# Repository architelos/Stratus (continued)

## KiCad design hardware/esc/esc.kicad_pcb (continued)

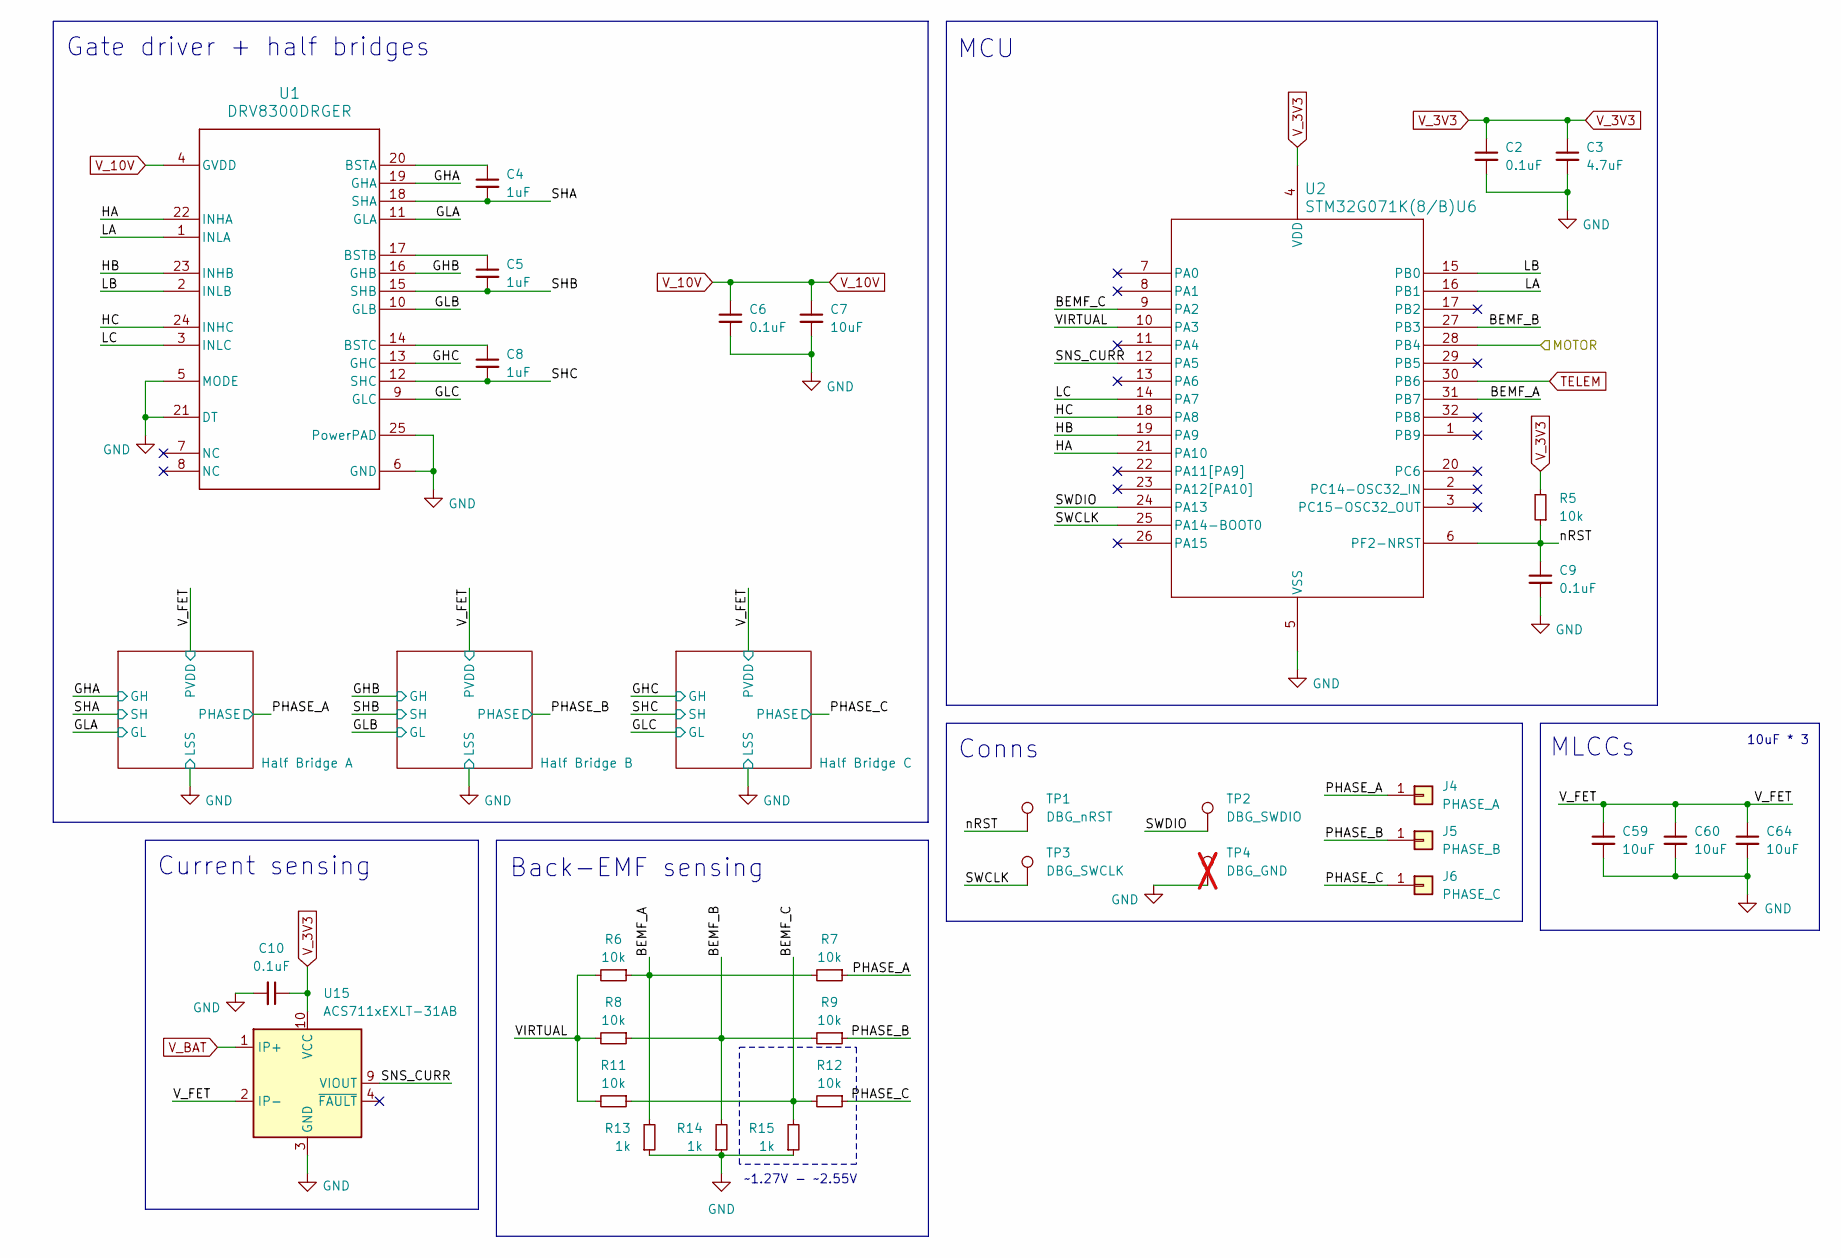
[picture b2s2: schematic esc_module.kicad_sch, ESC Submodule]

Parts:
C2, C6, C9, C10: 0.1uF; C_0402; MPN CGA2B3X7R1V104KT0Y0F; LCSC# C343047
C3: 4.7uF; C_0402; MPN TDK105CBJ475MV-F; LCSC# C22385335
C4, C5, C8: 1uF; C_0402; MPN GRM155R6YA105KE11J; LCSC# C3835721
C7: 10uF; C_1206_3216Metric; MPN GRT31CR6YA106KE01L; LCSC# C2175512
C59, C60, C64: 10uF; C_0805_2012Metric; MPN GRM21BR6YA106KE43L; LCSC# C162422
J4: PHASE_A; Phase_Pad_3x3_D1.5
J5: PHASE_B; Phase_Pad_3x3_D1.5
J6: PHASE_C; Phase_Pad_3x3_D1.5
R5, R6, R7, R8, R9, R11, R12: 10k; R_0402; MPN RC0402FR-0710KL; LCSC# C60490
R13, R14, R15: 1k; R_0402; MPN RC0402FR-071KL; LCSC# C106235
TP1: DBG_nRST; Debug_Pad_D1
TP2: DBG_SWDIO; Debug_Pad_D1
TP3: DBG_SWCLK; Debug_Pad_D1
TP4: DBG_GND; Debug_Pad_D1; not fitted
U1: DRV8300DRGER; MPN DRV8300DRGER; LCSC# C3655801
U2: STM32G071K(8/B)U6; STM32G071K8U6; MPN STM32G071KBU3; LCSC# C724239
U15: ACS711xEXLT-31AB; ACS711KEXLT-31AB-T; MPN ACS711KEXLT-31AB-T; LCSC# C146412

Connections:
/ESC Module 1/BEMF_A: R6.1, R7.2, R13.2, U2.31 (PB7)
/ESC Module 1/BEMF_B: R8.1, R9.2, R14.2, U2.27 (PB3)
/ESC Module 1/BEMF_C: R11.1, R12.2, R15.2, U2.9 (PA2)
/ESC Module 1/GHA: U1.19 (GHA); also elsewhere on the board
/ESC Module 1/GHB: U1.16 (GHB); also elsewhere on the board
/ESC Module 1/GHC: U1.13 (GHC); also elsewhere on the board
/ESC Module 1/GLA: U1.11 (GLA); also elsewhere on the board
/ESC Module 1/GLB: U1.10 (GLB); also elsewhere on the board
/ESC Module 1/GLC: U1.9 (GLC); also elsewhere on the board
/ESC Module 1/HA: U1.22 (INHA), U2.21 (PA10)
/ESC Module 1/HB: U1.23 (INHB), U2.19 (PA9)
/ESC Module 1/HC: U1.24 (INHC), U2.18 (PA8)
/ESC Module 1/LA: U1.1 (INLA), U2.16 (PB1)
/ESC Module 1/LB: U1.2 (INLB), U2.15 (PB0)
/ESC Module 1/LC: U1.3 (INLC), U2.14 (PA7)
/ESC Module 1/PHASE_A: C4.2, J4.1 (Pin_1_1), R7.1, U1.18 (SHA); also elsewhere on the board
/ESC Module 1/PHASE_B: C5.2, J5.1 (Pin_1_1), R9.1, U1.15 (SHB); also elsewhere on the board
/ESC Module 1/PHASE_C: C8.2, J6.1 (Pin_1_1), R12.1, U1.12 (SHC); also elsewhere on the board
/ESC Module 1/SNS_CURR: U2.12 (PA5), U15.9 (VIOUT)
/ESC Module 1/SWCLK: TP3.1 (1_1), U2.25 (PA14-BOOT0)
/ESC Module 1/SWDIO: TP2.1 (1_1), U2.24 (PA13)
/ESC Module 1/VIRTUAL: R6.2, R8.2, R11.2, U2.10 (PA3)
/ESC Module 1/V_FET: C59.1, C60.1, C64.1, U15.2 (IP-); also elsewhere on the board
/ESC Module 1/nRST: C9.1, R5.1, TP1.1 (1_1), U2.6 (PF2-NRST)
/M1: U2.28 (PB4); also elsewhere on the board
GND: C2.2, C3.2, C6.2, C7.2, C9.2, C10.2, C59.2, C60.2, C64.2, R13.1, R14.1, R15.1, TP4.1, U1.5 (MODE), U1.6 (GND), U1.21 (DT), U1.25 (PowerPAD), U2.5 (VSS), U15.3 (GND); also elsewhere on the board
unnamed: C4.1, U1.20 (BSTA)
unnamed: C5.1, U1.17 (BSTB)
unnamed: C8.1, U1.14 (BSTC)
TELEM: U2.30 (PB6); also elsewhere on the board
V_3V3: C2.1, C3.1, C10.1, R5.2, U2.4 (VDD), U15.10 (VCC); also elsewhere on the board
V_10V: C6.1, C7.1, U1.4 (GVDD); also elsewhere on the board
V_BAT: U15.1 (IP+); also elsewhere on the board

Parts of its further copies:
C11, C15, C18, C19, C20, C24, C27, C28, C29, C33, C36, C37: 0.1uF; C_0402; MPN CGA2B3X7R1V104KT0Y0F; LCSC# C343047
C12, C21, C30: 4.7uF; C_0402; MPN TDK105CBJ475MV-F; LCSC# C22385335
C13, C14, C17, C22, C23, C26, C31, C32, C35: 1uF; C_0402; MPN GRM155R6YA105KE11J; LCSC# C3835721
C16, C25, C34: 10uF; C_1206_3216Metric; MPN GRT31CR6YA106KE01L; LCSC# C2175512
C73, C74, C75, C76, C77, C78, C79, C80, C81: 10uF; C_0805_2012Metric; MPN GRM21BR6YA106KE43L; LCSC# C162422
J7, J10, J13: PHASE_A; Phase_Pad_3x3_D1.5
J8, J11, J14: PHASE_B; Phase_Pad_3x3_D1.5
J9, J12, J15: PHASE_C; Phase_Pad_3x3_D1.5
R22, R23, R24, R25, R26, R28, R29, R39, R40, R41, R42, R43, R45, R46, R56, R57, R58, R59, R60, R62, R63: 10k; R_0402; MPN RC0402FR-0710KL; LCSC# C60490
R30, R31, R32, R47, R48, R49, R64, R65, R66: 1k; R_0402; MPN RC0402FR-071KL; LCSC# C106235
TP5, TP9, TP13: DBG_nRST; Debug_Pad_D1
TP6, TP10, TP14: DBG_SWDIO; Debug_Pad_D1
TP7, TP11, TP15: DBG_SWCLK; Debug_Pad_D1
U4, U7, U10: DRV8300DRGER; MPN DRV8300DRGER; LCSC# C3655801
U5, U8, U11: STM32G071K(8/B)U6; STM32G071K8U6; MPN STM32G071KBU3; LCSC# C724239
U16, U17, U18: ACS711xEXLT-31AB; ACS711KEXLT-31AB-T; MPN ACS711KEXLT-31AB-T; LCSC# C146412

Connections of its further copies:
/ESC Module 2/BEMF_A: R23.1, R24.2, R30.2, U5.31 (PB7)
/ESC Module 2/BEMF_B: R25.1, R26.2, R31.2, U5.27 (PB3)
/ESC Module 2/BEMF_C: R28.1, R29.2, R32.2, U5.9 (PA2)
/ESC Module 2/GHA: U4.19 (GHA); also elsewhere on the board
/ESC Module 2/GHB: U4.16 (GHB); also elsewhere on the board
/ESC Module 2/GHC: U4.13 (GHC); also elsewhere on the board
/ESC Module 2/GLA: U4.11 (GLA); also elsewhere on the board
/ESC Module 2/GLB: U4.10 (GLB); also elsewhere on the board
/ESC Module 2/GLC: U4.9 (GLC); also elsewhere on the board
/ESC Module 2/HA: U4.22 (INHA), U5.21 (PA10)
/ESC Module 2/HB: U4.23 (INHB), U5.19 (PA9)
/ESC Module 2/HC: U4.24 (INHC), U5.18 (PA8)
/ESC Module 2/LA: U4.1 (INLA), U5.16 (PB1)
/ESC Module 2/LB: U4.2 (INLB), U5.15 (PB0)
/ESC Module 2/LC: U4.3 (INLC), U5.14 (PA7)
/ESC Module 2/PHASE_A: C13.2, J7.1 (Pin_1_1), R24.1, U4.18 (SHA); also elsewhere on the board
/ESC Module 2/PHASE_B: C14.2, J8.1 (Pin_1_1), R26.1, U4.15 (SHB); also elsewhere on the board
/ESC Module 2/PHASE_C: C17.2, J9.1 (Pin_1_1), R29.1, U4.12 (SHC); also elsewhere on the board
/ESC Module 2/SNS_CURR: U5.12 (PA5), U16.9 (VIOUT)
/ESC Module 2/SWCLK: TP7.1 (1_1), U5.25 (PA14-BOOT0)
/ESC Module 2/SWDIO: TP6.1 (1_1), U5.24 (PA13)
/ESC Module 2/VIRTUAL: R23.2, R25.2, R28.2, U5.10 (PA3)
/ESC Module 2/V_FET: C73.1, C74.1, C75.1, U16.2 (IP-); also elsewhere on the board
/ESC Module 2/nRST: C18.1, R22.1, TP5.1 (1_1), U5.6 (PF2-NRST)
/ESC Module 3/BEMF_A: R40.1, R41.2, R47.2, U8.31 (PB7)
/ESC Module 3/BEMF_B: R42.1, R43.2, R48.2, U8.27 (PB3)
/ESC Module 3/BEMF_C: R45.1, R46.2, R49.2, U8.9 (PA2)
/ESC Module 3/GHA: U7.19 (GHA); also elsewhere on the board
/ESC Module 3/GHB: U7.16 (GHB); also elsewhere on the board
/ESC Module 3/GHC: U7.13 (GHC); also elsewhere on the board
/ESC Module 3/GLA: U7.11 (GLA); also elsewhere on the board
/ESC Module 3/GLB: U7.10 (GLB); also elsewhere on the board
/ESC Module 3/GLC: U7.9 (GLC); also elsewhere on the board
/ESC Module 3/HA: U7.22 (INHA), U8.21 (PA10)
/ESC Module 3/HB: U7.23 (INHB), U8.19 (PA9)
/ESC Module 3/HC: U7.24 (INHC), U8.18 (PA8)
/ESC Module 3/LA: U7.1 (INLA), U8.16 (PB1)
/ESC Module 3/LB: U7.2 (INLB), U8.15 (PB0)
/ESC Module 3/LC: U7.3 (INLC), U8.14 (PA7)
/ESC Module 3/PHASE_A: C22.2, J10.1 (Pin_1_1), R41.1, U7.18 (SHA); also elsewhere on the board
/ESC Module 3/PHASE_B: C23.2, J11.1 (Pin_1_1), R43.1, U7.15 (SHB); also elsewhere on the board
/ESC Module 3/PHASE_C: C26.2, J12.1 (Pin_1_1), R46.1, U7.12 (SHC); also elsewhere on the board
/ESC Module 3/SNS_CURR: U8.12 (PA5), U17.9 (VIOUT)
/ESC Module 3/SWCLK: TP11.1 (1_1), U8.25 (PA14-BOOT0)
/ESC Module 3/SWDIO: TP10.1 (1_1), U8.24 (PA13)
/ESC Module 3/VIRTUAL: R40.2, R42.2, R45.2, U8.10 (PA3)
/ESC Module 3/V_FET: C76.1, C77.1, C78.1, U17.2 (IP-); also elsewhere on the board
/ESC Module 3/nRST: C27.1, R39.1, TP9.1 (1_1), U8.6 (PF2-NRST)
/ESC Module 4/BEMF_A: R57.1, R58.2, R64.2, U11.31 (PB7)
/ESC Module 4/BEMF_B: R59.1, R60.2, R65.2, U11.27 (PB3)
/ESC Module 4/BEMF_C: R62.1, R63.2, R66.2, U11.9 (PA2)
/ESC Module 4/GHA: U10.19 (GHA); also elsewhere on the board
/ESC Module 4/GHB: U10.16 (GHB); also elsewhere on the board
/ESC Module 4/GHC: U10.13 (GHC); also elsewhere on the board
/ESC Module 4/GLA: U10.11 (GLA); also elsewhere on the board
/ESC Module 4/GLB: U10.10 (GLB); also elsewhere on the board
/ESC Module 4/GLC: U10.9 (GLC); also elsewhere on the board
/ESC Module 4/HA: U10.22 (INHA), U11.21 (PA10)
/ESC Module 4/HB: U10.23 (INHB), U11.19 (PA9)
/ESC Module 4/HC: U10.24 (INHC), U11.18 (PA8)
/ESC Module 4/LA: U10.1 (INLA), U11.16 (PB1)
/ESC Module 4/LB: U10.2 (INLB), U11.15 (PB0)
/ESC Module 4/LC: U10.3 (INLC), U11.14 (PA7)
/ESC Module 4/PHASE_A: C31.2, J13.1 (Pin_1_1), R58.1, U10.18 (SHA); also elsewhere on the board
/ESC Module 4/PHASE_B: C32.2, J14.1 (Pin_1_1), R60.1, U10.15 (SHB); also elsewhere on the board
/ESC Module 4/PHASE_C: C35.2, J15.1 (Pin_1_1), R63.1, U10.12 (SHC); also elsewhere on the board
/ESC Module 4/SNS_CURR: U11.12 (PA5), U18.9 (VIOUT)
/ESC Module 4/SWCLK: TP15.1 (1_1), U11.25 (PA14-BOOT0)
/ESC Module 4/SWDIO: TP14.1 (1_1), U11.24 (PA13)
/ESC Module 4/VIRTUAL: R57.2, R59.2, R62.2, U11.10 (PA3)
/ESC Module 4/V_FET: C79.1, C80.1, C81.1, U18.2 (IP-); also elsewhere on the board
/ESC Module 4/nRST: C36.1, R56.1, TP13.1 (1_1), U11.6 (PF2-NRST)
/M2: U5.28 (PB4); also elsewhere on the board
/M3: U8.28 (PB4); also elsewhere on the board
/M4: U11.28 (PB4); also elsewhere on the board
GND: C11.2, C12.2, C15.2, C16.2, C18.2, C19.2, C20.2, C21.2, C24.2, C25.2, C27.2, C28.2, C29.2, C30.2, C33.2, C34.2, C36.2, C37.2, C73.2, C74.2, C75.2, C76.2, C77.2, C78.2, C79.2, C80.2, C81.2, R30.1, R31.1, R32.1, R47.1, R48.1, R49.1, R64.1, R65.1, R66.1, U4.5 (MODE), U4.6 (GND), U4.21 (DT), U4.25 (PowerPAD), U5.5 (VSS), U7.5 (MODE), U7.6 (GND), U7.21 (DT), U7.25 (PowerPAD), U8.5 (VSS), U10.5 (MODE), U10.6 (GND), U10.21 (DT), U10.25 (PowerPAD), U11.5 (VSS), U16.3 (GND), U17.3 (GND), U18.3 (GND); also elsewhere on the board
unnamed: C13.1, U4.20 (BSTA)
unnamed: C14.1, U4.17 (BSTB)
unnamed: C17.1, U4.14 (BSTC)
unnamed: C22.1, U7.20 (BSTA)
unnamed: C23.1, U7.17 (BSTB)
unnamed: C26.1, U7.14 (BSTC)
unnamed: C31.1, U10.20 (BSTA)
unnamed: C32.1, U10.17 (BSTB)
unnamed: C35.1, U10.14 (BSTC)
TELEM: U5.30 (PB6), U8.30 (PB6), U11.30 (PB6); also elsewhere on the board
V_3V3: C11.1, C12.1, C19.1, C20.1, C21.1, C28.1, C29.1, C30.1, C37.1, R22.2, R39.2, R56.2, U5.4 (VDD), U8.4 (VDD), U11.4 (VDD), U16.10 (VCC), U17.10 (VCC), U18.10 (VCC); also elsewhere on the board
V_10V: C15.1, C16.1, C24.1, C25.1, C33.1, C34.1, U4.4 (GVDD), U7.4 (GVDD), U10.4 (GVDD); also elsewhere on the board
V_BAT: U16.1 (IP+), U17.1 (IP+), U18.1 (IP+); also elsewhere on the board

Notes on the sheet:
Current sensing
10uF * 3
Back-EMF sensing
Gate driver + half bridges
MLCCs
MCU
Conns
~1.27V - ~2.55V

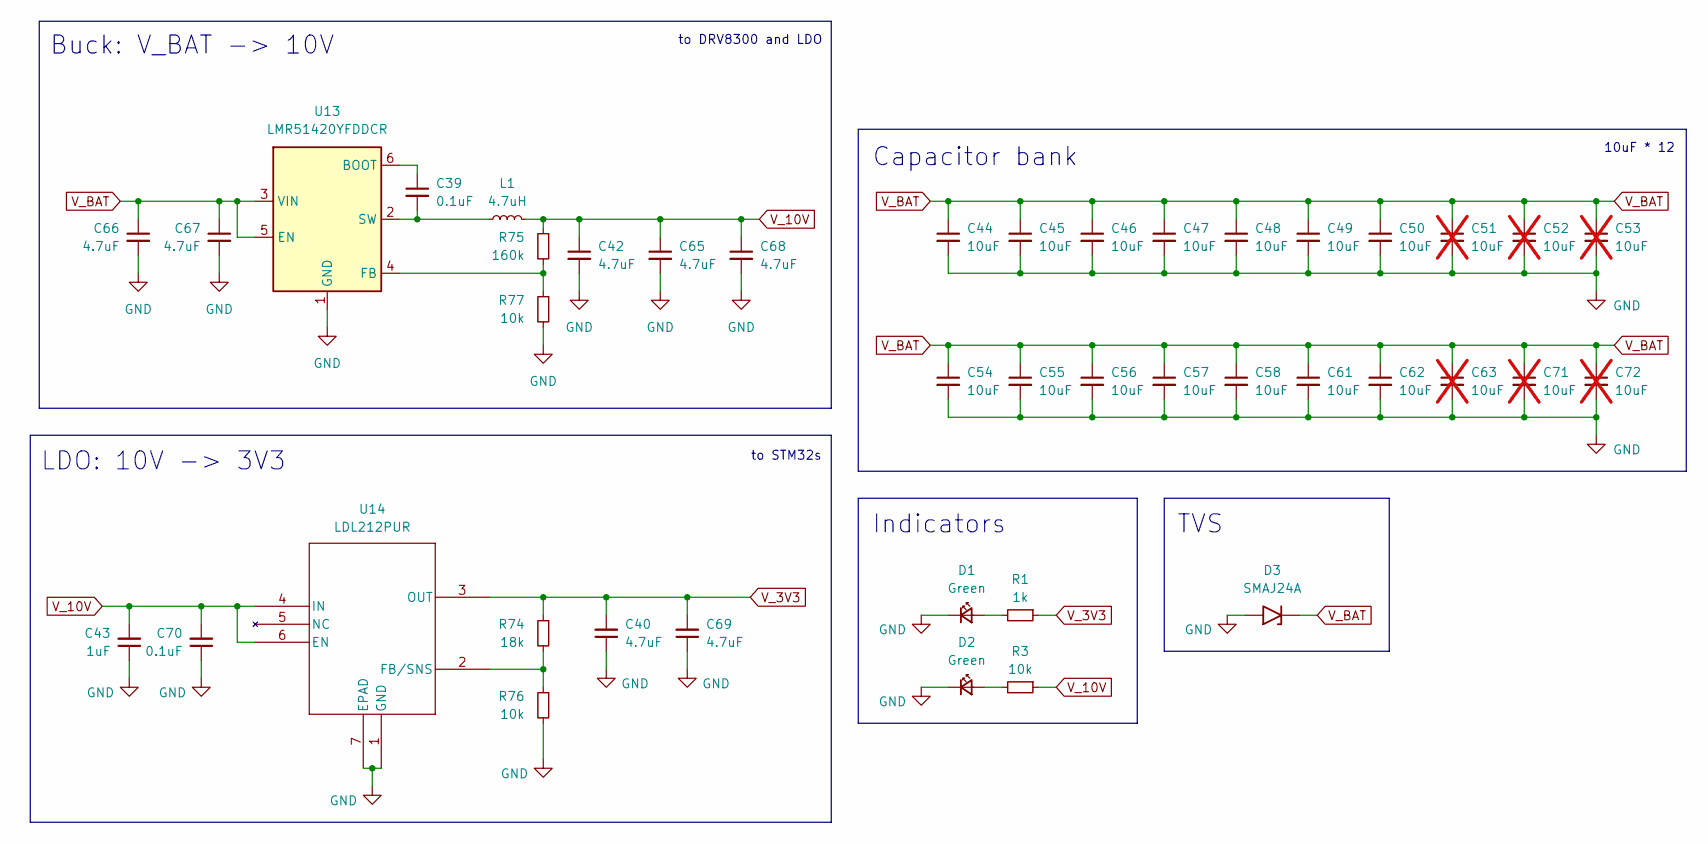
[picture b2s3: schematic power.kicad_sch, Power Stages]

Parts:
C39, C70: 0.1uF; C_0402; MPN CGA2B3X7R1V104KT0Y0F; LCSC# C343047
C40, C42, C65, C68, C69: 4.7uF; C_0402; MPN TDK105CBJ475MV-F; LCSC# C22385335
C43: 1uF; C_0402; MPN GRM155R6YA105KE11J; LCSC# C3835721
C44, C45, C46, C47, C48, C49, C50, C54, C55, C56, C57, C58, C61, C62: 10uF; C_0805_2012Metric; MPN GRM21BR6YA106KE43L; LCSC# C162422
C51, C52, C53, C63, C71, C72: 10uF; C_0805_2012Metric; MPN GRM21BR6YA106KE43L; LCSC# C162422; not fitted
C66, C67: 4.7uF; C_0603_1608Metric; MPN CL10A475KL8NRNC; LCSC# C307467
D1, D2: Green; LED_0603_1608Metric; MPN VLMTG1400-GS08; LCSC# C3000897
D3: SMAJ24A; SMAJ20A; MPN SMAJ24A; LCSC# C148222
L1: 4.7uH; L_1210_3225Metric; MPN BCL322520RT-4R7M-D; LCSC# C3224690
R1: 1k; R_0402; MPN RC0402FR-071KL; LCSC# C106235
R3, R76, R77: 10k; R_0402; MPN RC0402FR-0710KL; LCSC# C60490
R74: 18k; R_0402; MPN RC0402FR-0718KL; LCSC# C138044
R75: 160k; R_0402; MPN AC0402FR-07160KL; LCSC# C226798
U13: LMR51420YFDDCR; MPN LMR51420YFDDCR; LCSC# C7296200
U14: LDL212PUR; LDLPUR212; MPN LDL212PUR; LCSC# C2969849

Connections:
GND: C40.1, C42.2, C43.1, C44.2, C45.2, C46.2, C47.2, C48.2, C49.2, C50.2, C51.2, C52.2, C53.2, C54.2, C55.2, C56.2, C57.2, C58.2, C61.2, C62.2, C63.2, C65.2, C66.2, C67.2, C68.2, C69.1, C70.1, C71.2, C72.2, D1.1 (K), D2.1 (K), D3.2 (A2), R76.2, R77.2, U13.1 (GND), U14.1 (GND), U14.7 (EPAD); also elsewhere on the board
unnamed: D1.2 (A), R1.2
unnamed: D2.2 (A), R3.2
unnamed: C39.1, U13.6 (BOOT)
unnamed: R75.2, R77.1, U13.4 (FB)
unnamed: C39.2, L1.1, U13.2 (SW)
unnamed: R74.2, R76.1, U14.2 (FB/SNS)
V_3V3: C40.2, C69.2, R1.1, R74.1, U14.3 (OUT); also elsewhere on the board
V_10V: C42.1, C43.2, C65.1, C68.1, C70.2, L1.2, R3.1, R75.1, U14.4 (IN), U14.6 (EN); also elsewhere on the board
V_BAT: C44.1, C45.1, C46.1, C47.1, C48.1, C49.1, C50.1, C51.1, C52.1, C53.1, C54.1, C55.1, C56.1, C57.1, C58.1, C61.1, C62.1, C63.1, C66.1, C67.1, C71.1, C72.1, D3.1 (A1), U13.3 (VIN), U13.5 (EN); also elsewhere on the board

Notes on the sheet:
Buck: V_BAT -> 10V
Capacitor bank
to DRV8300 and LDO
to STM32s
10uF * 12
Indicators
LDO: 10V -> 3V3
TVS

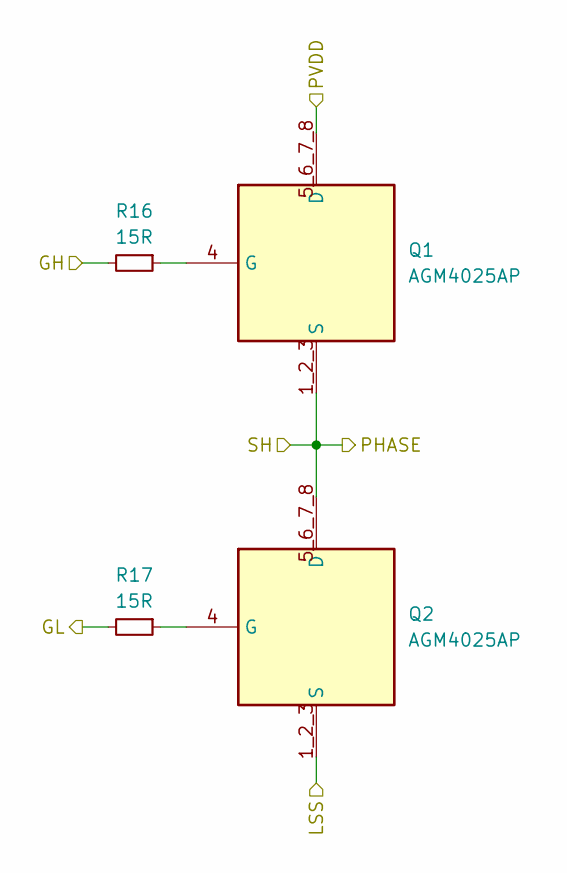
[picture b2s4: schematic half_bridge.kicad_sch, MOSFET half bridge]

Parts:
Q1, Q2: AGM4025AP; MPN AGM4025AP; LCSC# C42411651
R16, R17: 15R; R_0402; MPN RC0402FR-0715RL; LCSC# C138052

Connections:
/ESC Module 1/GHA: R16.2; also elsewhere on the board
/ESC Module 1/GLA: R17.2; also elsewhere on the board
/ESC Module 1/PHASE_A: Q1.1_2_3 (S), Q2.5_6_7_8 (D); also elsewhere on the board
/ESC Module 1/V_FET: Q1.5_6_7_8 (D); also elsewhere on the board
GND: Q2.1_2_3 (S); also elsewhere on the board
unnamed: Q1.4 (G), R16.1
unnamed: Q2.4 (G), R17.1

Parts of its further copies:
Q3, Q4, Q5, Q6, Q7, Q8, Q9, Q10, Q11, Q12, Q13, Q14, Q15, Q16, Q17, Q18, Q19, Q20, Q21, Q22, Q23, Q24: AGM4025AP; MPN AGM4025AP; LCSC# C42411651
R18, R19, R20, R21, R33, R34, R35, R36, R37, R38, R50, R51, R52, R53, R54, R55, R67, R68, R69, R70, R71, R72: 15R; R_0402; MPN RC0402FR-0715RL; LCSC# C138052

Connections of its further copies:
/ESC Module 1/GHB: R18.2; also elsewhere on the board
/ESC Module 1/GHC: R20.2; also elsewhere on the board
/ESC Module 1/GLB: R19.2; also elsewhere on the board
/ESC Module 1/GLC: R21.2; also elsewhere on the board
/ESC Module 1/PHASE_B: Q3.1_2_3 (S), Q4.5_6_7_8 (D); also elsewhere on the board
/ESC Module 1/PHASE_C: Q5.1_2_3 (S), Q6.5_6_7_8 (D); also elsewhere on the board
/ESC Module 1/V_FET: Q3.5_6_7_8 (D), Q5.5_6_7_8 (D); also elsewhere on the board
/ESC Module 2/GHA: R37.2; also elsewhere on the board
/ESC Module 2/GHB: R33.2; also elsewhere on the board
/ESC Module 2/GHC: R35.2; also elsewhere on the board
/ESC Module 2/GLA: R38.2; also elsewhere on the board
/ESC Module 2/GLB: R34.2; also elsewhere on the board
/ESC Module 2/GLC: R36.2; also elsewhere on the board
/ESC Module 2/PHASE_A: Q11.1_2_3 (S), Q12.5_6_7_8 (D); also elsewhere on the board
/ESC Module 2/PHASE_B: Q7.1_2_3 (S), Q8.5_6_7_8 (D); also elsewhere on the board
/ESC Module 2/PHASE_C: Q9.1_2_3 (S), Q10.5_6_7_8 (D); also elsewhere on the board
/ESC Module 2/V_FET: Q7.5_6_7_8 (D), Q9.5_6_7_8 (D), Q11.5_6_7_8 (D); also elsewhere on the board
/ESC Module 3/GHA: R54.2; also elsewhere on the board
/ESC Module 3/GHB: R50.2; also elsewhere on the board
/ESC Module 3/GHC: R52.2; also elsewhere on the board
/ESC Module 3/GLA: R55.2; also elsewhere on the board
/ESC Module 3/GLB: R51.2; also elsewhere on the board
/ESC Module 3/GLC: R53.2; also elsewhere on the board
/ESC Module 3/PHASE_A: Q17.1_2_3 (S), Q18.5_6_7_8 (D); also elsewhere on the board
/ESC Module 3/PHASE_B: Q13.1_2_3 (S), Q14.5_6_7_8 (D); also elsewhere on the board
/ESC Module 3/PHASE_C: Q15.1_2_3 (S), Q16.5_6_7_8 (D); also elsewhere on the board
/ESC Module 3/V_FET: Q13.5_6_7_8 (D), Q15.5_6_7_8 (D), Q17.5_6_7_8 (D); also elsewhere on the board
/ESC Module 4/GHA: R71.2; also elsewhere on the board
/ESC Module 4/GHB: R67.2; also elsewhere on the board
/ESC Module 4/GHC: R69.2; also elsewhere on the board
/ESC Module 4/GLA: R72.2; also elsewhere on the board
/ESC Module 4/GLB: R68.2; also elsewhere on the board
/ESC Module 4/GLC: R70.2; also elsewhere on the board
/ESC Module 4/PHASE_A: Q23.1_2_3 (S), Q24.5_6_7_8 (D); also elsewhere on the board
/ESC Module 4/PHASE_B: Q19.1_2_3 (S), Q20.5_6_7_8 (D); also elsewhere on the board
/ESC Module 4/PHASE_C: Q21.1_2_3 (S), Q22.5_6_7_8 (D); also elsewhere on the board
/ESC Module 4/V_FET: Q19.5_6_7_8 (D), Q21.5_6_7_8 (D), Q23.5_6_7_8 (D); also elsewhere on the board
GND: Q4.1_2_3 (S), Q6.1_2_3 (S), Q8.1_2_3 (S), Q10.1_2_3 (S), Q12.1_2_3 (S), Q14.1_2_3 (S), Q16.1_2_3 (S), Q18.1_2_3 (S), Q20.1_2_3 (S), Q22.1_2_3 (S), Q24.1_2_3 (S); also elsewhere on the board
unnamed: Q3.4 (G), R18.1
unnamed: Q4.4 (G), R19.1
unnamed: Q5.4 (G), R20.1
unnamed: Q6.4 (G), R21.1
unnamed: Q7.4 (G), R33.1
unnamed: Q8.4 (G), R34.1
unnamed: Q9.4 (G), R35.1
unnamed: Q10.4 (G), R36.1
unnamed: Q11.4 (G), R37.1
unnamed: Q12.4 (G), R38.1
unnamed: Q13.4 (G), R50.1
unnamed: Q14.4 (G), R51.1
unnamed: Q15.4 (G), R52.1
unnamed: Q16.4 (G), R53.1
unnamed: Q17.4 (G), R54.1
unnamed: Q18.4 (G), R55.1
unnamed: Q19.4 (G), R67.1
unnamed: Q20.4 (G), R68.1
unnamed: Q21.4 (G), R69.1
unnamed: Q22.4 (G), R70.1
unnamed: Q23.4 (G), R71.1
unnamed: Q24.4 (G), R72.1

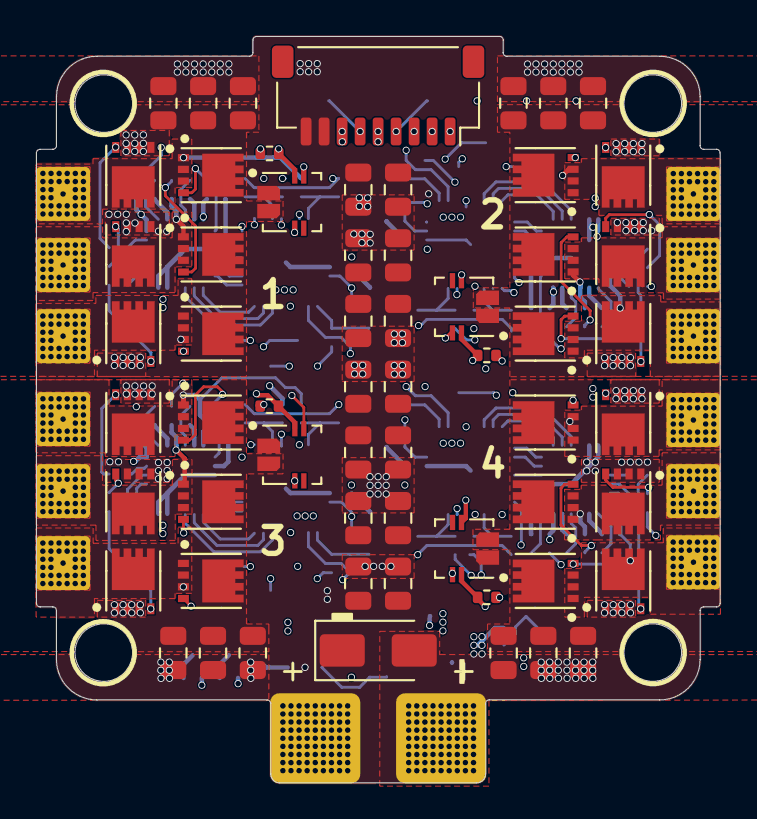
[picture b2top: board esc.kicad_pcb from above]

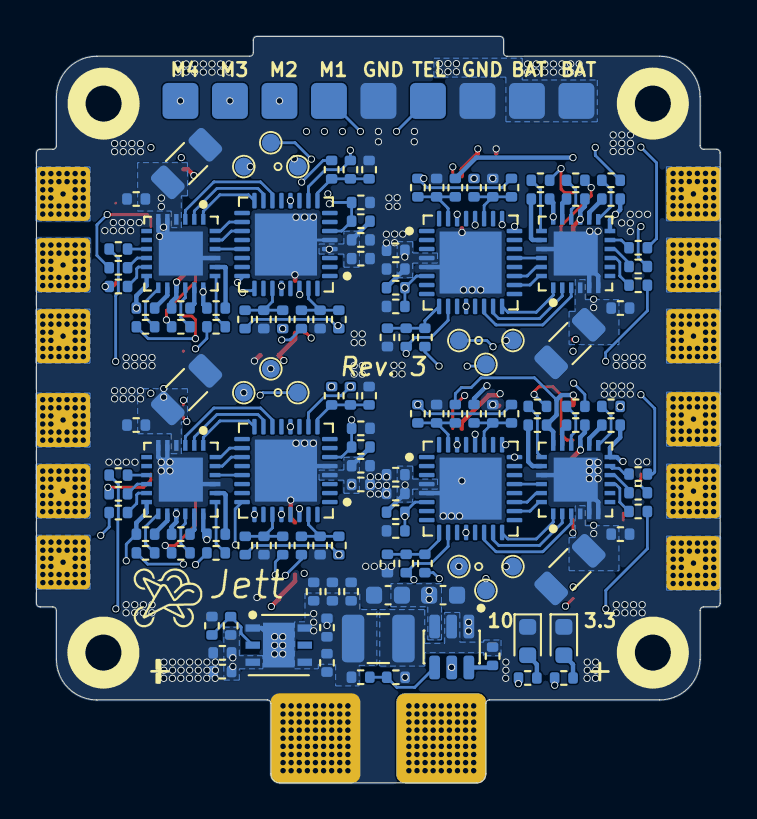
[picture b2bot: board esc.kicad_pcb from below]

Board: 8 copper layers, 38.0 x 41.5 mm, 215 parts (140 on the bottom side), 147 nets.

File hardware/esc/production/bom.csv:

"Reference","Qty","Value","MFR","MPN","LCSC#","Footprint","Description","DNP","Exclude from Board","Exclude from BOM","Datasheet"
"C2,C6,C9,C10,C11,C15,C18,C19,C20,C24,C27,C28,C29,C33,C36,C37,C39,C70","18","0.1uF","TDK","CGA2B3X7R1V104KT0Y0F","C343047","Stratus:C_0402","0402 0.1uF 35V","","","",""
"C3,C12,C21,C30,C40,C42,C65,C68,C69","9","4.7uF","Taiyo Yuden","TDK105CBJ475MV-F","C22385335","Stratus:C_0402","0402 4.7uF 25V","","","",""
"C4,C5,C8,C13,C14,C17,C22,C23,C26,C31,C32,C35,C43","13","1uF","Murata","GRM155R6YA105KE11J","C3835721","Stratus:C_0402","0402 1uF 35V","","","",""
"C7,C16,C25,C34","4","10uF","Murata","GRT31CR6YA106KE01L","C2175512","Capacitor_SMD:C_1206_3216Metric","1206 10uF 35V","","","",""
"C44,C45,C46,C47,C48,C49,C50,C54,C55,C56,C57,C58,C59,C60,C61,C62,C64,C73,C74,C75,C76,C77,C78,C79,C80,C81","26","10uF","Murata","GRM21BR6YA106KE43L","C162422","Capacitor_SMD:C_0805_2012Metric","0805 10uF 35V","","","",""
"C66,C67","2","4.7uF","Samsung","CL10A475KL8NRNC","C307467","Capacitor_SMD:C_0603_1608Metric","0603 4.7uF 35V","","","",""
"D1,D2","2","Green","Vishay","VLMTG1400-GS08","C3000897","LED_SMD:LED_0603_1608Metric","0603 Green LED","","","",""
"D3","1","SMAJ24A","Littelfuse","SMAJ24A","C148222","Stratus:SMAJ20A","38.9VC DO-214AC","","","","https://www.littelfuse.com/media?resourcetype=datasheets&ite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"
"J1","1","TO_FC","JST","SM09B-SRSS-TB(LF)(SN)","C160408","Stratus:JST_SH_1x9_ESC","Horizontal JST-SH 1x9","","","",""
"L1","1","4.7uH","TDK","BCL322520RT-4R7M-D","C3224690","Inductor_SMD:L_1210_3225Metric","1210 4.7uH 2.5A Isat","","","",""
"Q1,Q2,Q3,Q4,Q5,Q6,Q7,Q8,Q9,Q10,Q11,Q12,Q13,Q14,Q15,Q16,Q17,Q18,Q19,Q20,Q21,Q22,Q23,Q24","24","AGM4025AP","AGMSEMI","AGM4025AP","C42411651","Stratus:CSD17575Q3","N-Channel MOSFET 40V","","","","https://www.lcsc.com/datasheet/C42411651.pdf"
"R1,R13,R14,R15,R30,R31,R32,R47,R48,R49,R64,R65,R66","13","1k","Yageo","RC0402FR-071KL","C106235","Stratus:R_0402","0402 1k","","","",""
"R3,R5,R6,R7,R8,R9,R11,R12,R22,R23,R24,R25,R26,R28,R29,R39,R40,R41,R42,R43,R45,R46,R56,R57,R58,R59,R60,R62,R63,R76,R77","31","10k","Yageo","RC0402FR-0710KL","C60490","Stratus:R_0402","0402 10k","","","",""
"R16,R17,R18,R19,R20,R21,R33,R34,R35,R36,R37,R38,R50,R51,R52,R53,R54,R55,R67,R68,R69,R70,R71,R72","24","15R","Yageo","RC0402FR-0715RL","C138052","Stratus:R_0402","0402 15R","","","",""
"R74","1","18k","Yageo","RC0402FR-0718KL","C138044","Stratus:R_0402","0402 18k","","","",""
"R75","1","160k","Yageo","AC0402FR-07160KL","C226798","Stratus:R_0402","0402 160k","","","",""
"U1,U4,U7,U10","4","DRV8300DRGER","TI","DRV8300DRGER","C3655801","Stratus:DRV8300DRGER","https://www.lcsc.com/datasheet/C3655801.pdf","","","","https://www.ti.com/lit/gpn/drv8300"
"U2,U5,U8,U11","4","STM32G071K(8/B)U6","ST","STM32G071KBU3","C724239","Stratus:STM32G071K8U6","https://www.lcsc.com/datasheet/C724237.pdf","","","","https://www.st.com/resource/en/datasheet/stm32g071k8.pdf"
"U13","1","LMR51420YFDDCR","TI","LMR51420YFDDCR","C7296200","Stratus:LMR51420YFDDCR","4.5-V to 36-V, 2-A, Synchronous Buck Converter","","","","ti.com/lit/ds/symlink/lmr51420.pdf"
"U14","1","LDL212PUR","ST","LDL212PUR","C2969849","Stratus:LDLPUR212","1.18V~17.3V Positive Adjustable DFN-6(3x3)","","","","https://www.lcsc.com/datasheet/C2969849.pdf"
"U15,U16,U17,U18","4","ACS711xEXLT-31AB","Allegro","ACS711KEXLT-31AB-T","C146412","Stratus:ACS711KEXLT-31AB-T","±31A Bidirectional, Hall-Effect Current Sensor, +3.3V supply, 45mV/A, QFN-12","","","","http://www.allegromicro.com/~/Media/Files/Datasheets/ACS711-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"
